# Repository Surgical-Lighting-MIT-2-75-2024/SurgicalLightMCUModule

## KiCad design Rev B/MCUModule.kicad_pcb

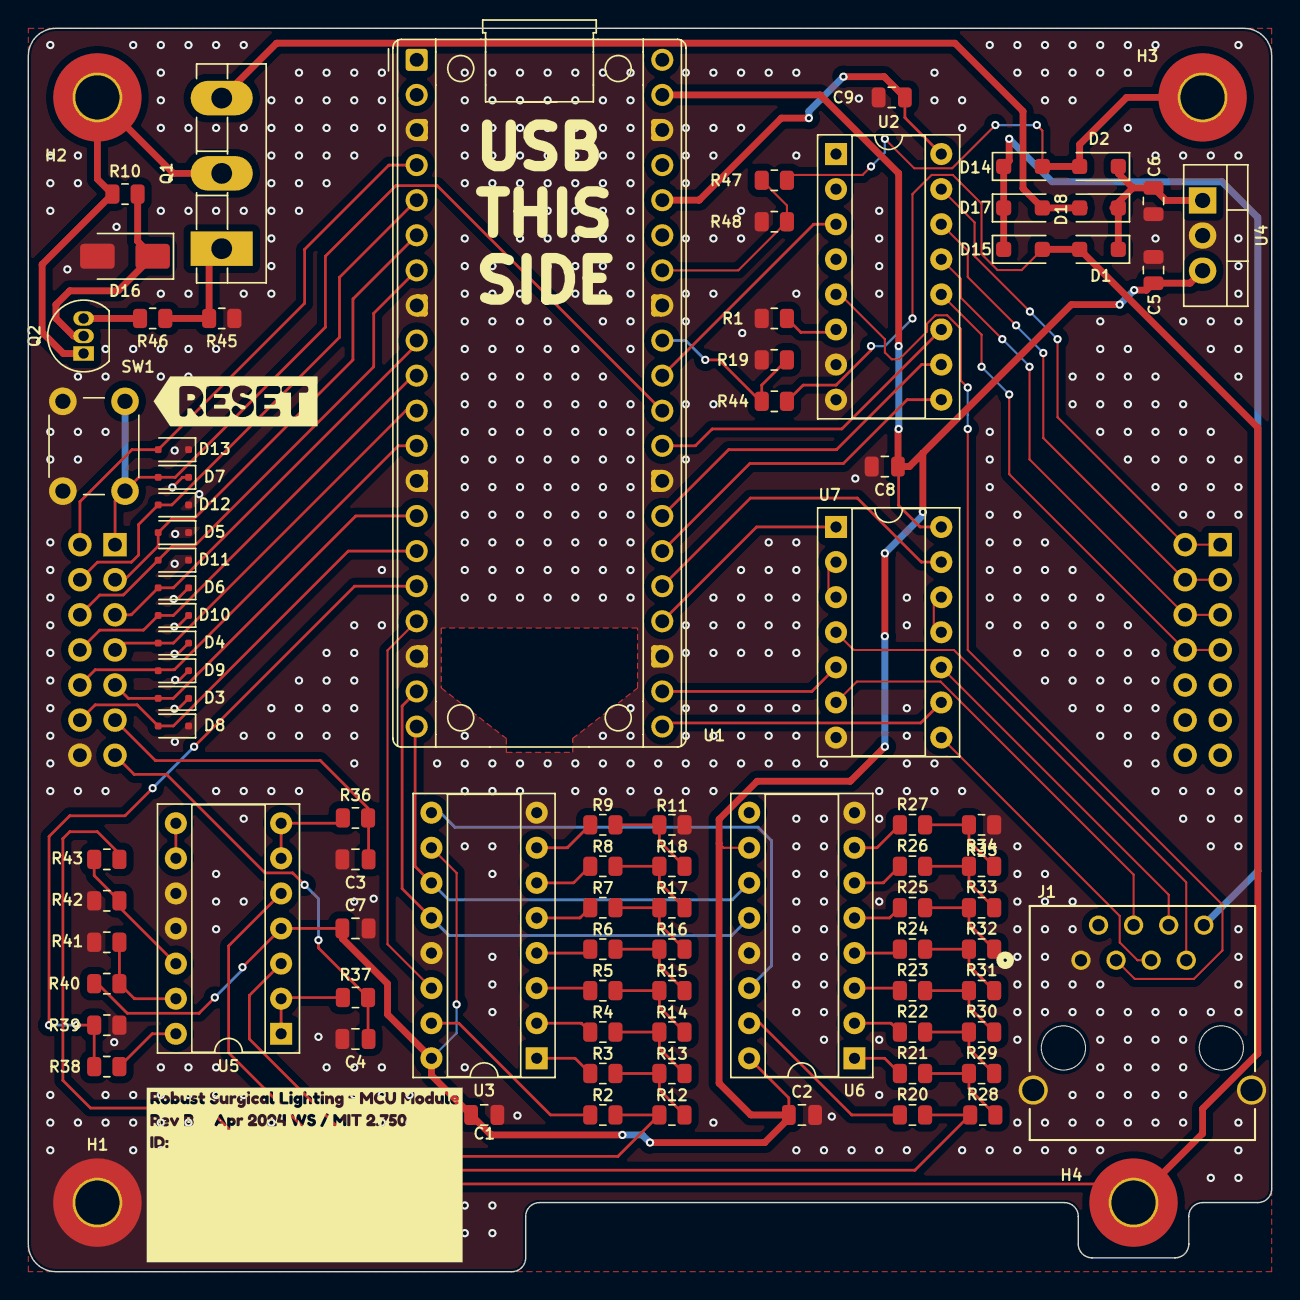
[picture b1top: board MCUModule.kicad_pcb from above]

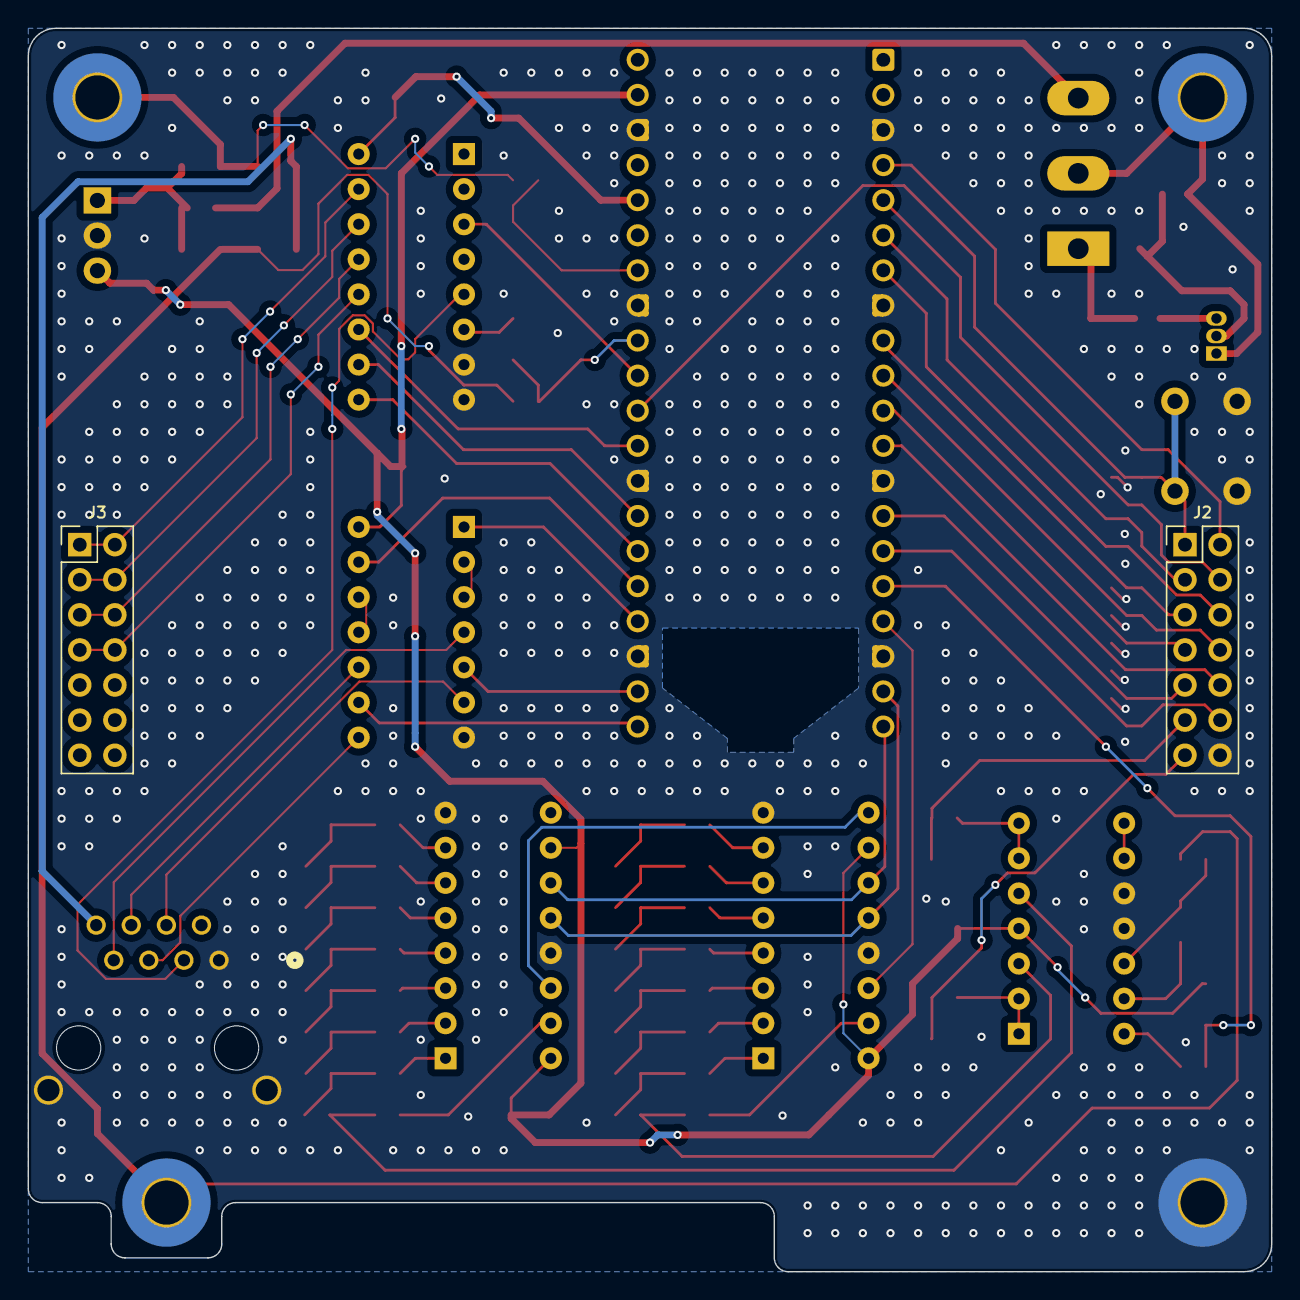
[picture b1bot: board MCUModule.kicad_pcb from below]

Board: 2 copper layers, 90.0 x 90.0 mm, 94 parts (2 on the bottom side), 90 nets.

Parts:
C1, C2, C7, C8, C9: 100nF 50V,X7R; C_0805_2012Metric
C3, C4, C5, C6: 1uF 50V,X7R; C_0805_2012Metric
D1, D2, D14, D15, D17, D18: 1N5819W; D_SOD-123F
D3, D4, D5, D6, D7, D8, D9, D10, D11, D12, D13: PESD3V3L1BA,115; D_SOD-323F
D16: SMAZ15Z-13-F; D_SMA
H1, H2, H3, H4: M3 Hole; MountingHole_3.2mm_M3_Pad_TopBottom
J1: RJ45_Shielded; CONN_A-2014-2S-4-N-R_ASM
J2, J3: 2x7 P2.54mm; PinHeader_2x07_P2.54mm_Vertical
Q1: TIP35C; TO-3PB-3_Vertical
Q2: BC337; TO-92_Inline
R1: 0; R_0805_2012Metric
R2, R3, R4, R5, R6, R7, R8, R9, R11, R20, R21, R22, R23, R24, R25, R26, R27, R35: 20k; R_0805_2012Metric
R10, R12, R13, R14, R15, R16, R17, R18, R19, R28, R29, R30, R31, R32, R33, R34, R39, R40, R41, R42, R46, R48: 10k; R_0805_2012Metric
R36, R37: 1k; R_0805_2012Metric
R38: 4.7k; R_0805_2012Metric
R43, R45: 27k; R_0805_2012Metric
R44, R47: 33k; R_0805_2012Metric
SW1: SW_SPST; SW_PUSH_6mm
U1: RaspberryPi_Pico; RaspberryPi_Pico_Common_THT
U2: 74HC4051; DIP-16_W7.62mm_Socket
U3, U6: 74HC595; DIP-16_W7.62mm_Socket
U4: LM7805_TO220; TO-220-3_Vertical
U5: LM324; DIP-14_W7.62mm_Socket
U7: 74HC14; DIP-14_W7.62mm_Socket
kibuzzard-6626A9C6: G***; kibuzzard-6626A9C6
kibuzzard-662436D7: G***; kibuzzard-662436D7

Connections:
+3.3V: C9.1, U1.36 (3V3), U2.16 (VCC)
+5V: C1.1, C2.1, C5.1, C7.1, C8.1, R40.2, U1.39 (VSYS), U3.10 (~SRCLR), U3.16 (VCC), U4.3 (VO), U5.4 (V+), U6.10 (~SRCLR), U6.16 (VCC), U7.14 (VCC)
/11V_SOLAR: D17.2 (A), D18.2 (A), Q1.3 (E)
/12V_Battery: D2.2 (A), D14.2 (A), H3.1, R47.2
/12V_Wall: D1.2 (A), D15.2 (A), H4.1, R43.1, R44.2
/12V_Wall_Bad: R38.2, R39.1, U1.16 (GPIO12)
/15V_SOLAR: Q1.1 (B), R45.2, R46.1
/AnalogMuxOut: U1.31 (GPIO26_ADC0), U2.3 (A)
/BatChgEna1: D4.2 (A2), J2.7, U1.11 (GPIO8)
/BatChgEna2: D3.2 (A2), J2.9, U1.14 (GPIO10)
/BoostEna1: D5.2 (A2), J2.3, U1.6 (GPIO4)
/BoostEna2: D6.2 (A2), J2.5, U1.9 (GPIO6)
/BoostVoltage_0.1x: J3.7, J3.8, U2.12 (A3)
/DATA_5V: J1.7, U7.4
/DATA_DAC: U1.17 (GPIO13), U3.14 (SER)
/DATA_DISPLAY: U1.24 (GPIO18), U7.1
/DIM: J1.3, U2.5 (A5)
/DisableBackupPico: D13.2 (A2), J2.2, U1.4 (GPIO2)
/IRef_Buck: C3.1, J2.11, R36.2
/LightISense1: J3.5, J3.6, U2.13 (A0)
/LightISense2: J3.3, J3.4, U2.14 (A1)
/ModuleENA: D7.2 (A2), J2.1, SW1.2 (B), U1.30 (RUN)
/Mux2: J3.1, J3.2, U2.15 (A2)
/OE_5V: J1.4, U7.6
/OE_DISPLAY: U1.22 (GPIO17), U7.5
/PWM_Lights1: D10.2 (A2), J2.8, U1.10 (GPIO7)
/PWM_Lights2: D9.2 (A2), J2.10, U1.12 (GPIO9)
/PowerModuleEna1: D12.2 (A2), J2.4, U1.5 (GPIO3)
/PowerModuleEna2: D11.2 (A2), J2.6, U1.7 (GPIO5)
/RCLK_5V: J1.5, U7.8
/RelaySelectHighPreference: D8.2 (A2), J2.12, U1.15 (GPIO11)
/S0: U1.29 (GPIO22), U2.11 (S0)
/S1: U1.27 (GPIO21), U2.10 (S1)
/S2: U1.26 (GPIO20), U2.9 (S2)
/SOLAR: H2.1, Q1.2 (C), Q2.1 (C), R10.1
/SRCLK_5V: J1.6, U7.10
/SRCLK_DISPLAY: U1.25 (GPIO19), U7.13
/Shift Register Based DAC 0/AnalogOut_Unbuffered: R2.2, R12.1, U5.3 (+)
/Shift Register Based DAC 0/DataOut: U3.9 (QH'), U6.14 (SER)
/Shift Register Based DAC 1/AnalogOut_Unbuffered: R20.2, R28.1, U5.5 (+)
/VRef_Buck: C4.1, J2.13, R37.2
/~RCLK_DISPLAY: U1.21 (GPIO16), U7.9
GND: C1.2, C2.2, C3.2, C4.2, C5.2, C6.2, C7.2, C8.2, C9.2, D3.1 (A1), D4.1 (A1), D5.1 (A1), D6.1 (A1), D7.1 (A1), D8.1 (A1), D9.1 (A1), D10.1 (A1), D11.1 (A1), D12.1 (A1), D13.1 (A1), D16.2 (A), H1.1, J1.1, J1.SH, J2.14, R1.2, R11.1, R19.1, R35.1, R39.2, R41.2, R42.2, R45.1, R48.1, SW1.1 (A), U1.3 (GND), U1.8 (GND), U1.13 (GND), U1.18 (GND), U1.23 (GND), U1.28 (GND), U1.33 (AGND), U1.38 (GND), U2.7 (VEE), U2.8 (GND), U3.8 (GND), U3.13 (~OE), U4.2 (GND), U5.10 (+), U5.11 (V-), U6.8 (GND), U6.13 (~OE), U7.7 (GND)
unnamed: C6.1, D1.1 (K), D2.1 (K), D18.1 (K), U4.1 (VI)
unnamed: D14.1 (K), D15.1 (K), D17.1 (K), J1.8
unnamed: D16.1 (K), Q2.2 (B), R10.2
unnamed: Q2.3 (E), R46.2
unnamed: R9.2, R11.2, R18.2
unnamed: R3.2, R12.2, R13.1
unnamed: R4.2, R13.2, R14.1
unnamed: R5.2, R14.2, R15.1
unnamed: R6.2, R15.2, R16.1
unnamed: R7.2, R16.2, R17.1
unnamed: R8.2, R17.2, R18.1
unnamed: R21.2, R28.2, R29.1
unnamed: R22.2, R29.2, R30.1
unnamed: R23.2, R30.2, R31.1
unnamed: R24.2, R31.2, R32.1
unnamed: R25.2, R32.2, R33.1
unnamed: R26.2, R33.2, R34.1
unnamed: R27.2, R34.2, R35.2
unnamed: R38.1, U5.14
unnamed: R19.2, R44.1, U1.32 (GPIO27_ADC1)
unnamed: R47.1, R48.2, U1.34 (GPIO28_ADC2)
unnamed: R1.1, U2.6 (~E)
unnamed: R2.1, U3.15 (QA)
unnamed: R3.1, U3.1 (QB)
unnamed: R4.1, U3.2 (QC)
unnamed: R5.1, U3.3 (QD)
unnamed: R6.1, U3.4 (QE)
unnamed: R7.1, U3.5 (QF)
unnamed: R8.1, U3.6 (QG)
unnamed: R9.1, U3.7 (QH)
unnamed: R37.1, U5.1, U5.2 (-)
unnamed: R36.1, U5.6 (-), U5.7
unnamed: U5.8, U5.9 (-)
unnamed: R42.1, R43.2, U5.12 (+)
unnamed: R40.1, R41.1, U5.13 (-)
unnamed: R20.1, U6.15 (QA)
unnamed: R21.1, U6.1 (QB)
unnamed: R22.1, U6.2 (QC)
unnamed: R23.1, U6.3 (QD)
unnamed: R24.1, U6.4 (QE)
unnamed: R25.1, U6.5 (QF)
unnamed: R26.1, U6.6 (QG)
unnamed: R27.1, U6.7 (QH)
unnamed: U7.2, U7.3
unnamed: U7.11, U7.12
RCLK_DAC: U1.19 (GPIO14), U3.12 (RCLK), U6.12 (RCLK)
SRCLK_DAC: U1.20 (GPIO15), U3.11 (SRCLK), U6.11 (SRCLK)

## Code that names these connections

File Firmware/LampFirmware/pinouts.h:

#ifdef REV_A01

#define RCLK_DISPLAY 16
#define OE_DISPLAY 17
#define DATA_DISPLAY 18
#define SRCLK_DISPLAY 19

#define RCLK_DAC 14
#define DATA_DAC 15
#define SRCLK_DAC 13

#define MUX_S0 22
#define MUX_S1 21
#define MUX_S2 20
#define MUX_ADC 26

#define BRIGHTNESS_POT_CHANNEL 3
#define SOLAR_SENSE_CHANNEL 5

#define RELAY 11

#define PWM1 7
#define WallBadINT 12
#define WallSense 27
#define BatterySense 28

#endif

#ifdef REV_B01

#define RCLK_DISPLAY 16
#define OE_DISPLAY 17
#define DATA_DISPLAY 18
#define SRCLK_DISPLAY 19

#define RCLK_DAC 14
#define DATA_DAC 13
#define SRCLK_DAC 15

#define MUX_S0 22
#define MUX_S1 21
#define MUX_S2 20
#define MUX_ADC 26

#define BRIGHTNESS_POT_CHANNEL 5
#define SOLAR_SENSE_CHANNEL 3

#define RELAY 11

#define PWM1 7
#define WallBadINT 12
#define WallSense 27
#define BatterySense 28

#endif

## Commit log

2024-03-20 Started schematic
2024-03-27 Edit File Folders to reflect Revisioning Standards
2024-03-29 added more schematic stuffs
2024-04-03 routed
2024-04-03 updated BOM
2024-04-13 Added firmware
2024-04-18 added power module support
2024-04-24 edited mcu code weeee
2024-04-25 updated bits
2024-04-25 i has perfect c0d3
2024-04-25 perfect code
2024-05-07 added status indication code weeee
2024-05-08 fixed pinouts + battery cap calc
2024-05-08 updated code to work with buck setpoint control
2024-05-14 added solar compatibility
